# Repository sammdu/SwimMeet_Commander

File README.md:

# Swim Meet Commander

#### Unofficial macro keyboard for the [HY-TEK Swim Meet Manager](https://hytek.active.com/swim-meet-software.html) software.   

Designed with [KiCad](https://www.kicad-pcb.org/)   
Programmed with [Arduino](https://www.arduino.cc/)   

&nbsp;&nbsp;

## What Is This

A macro keyboard that controls the swim meet scoring software commonly used in American high-school and college swim meets. It simplifies operation of the software by pulling out 13 most used functionalities as dedicated keys, achieving one-key operation.

The device works by triggering keyboard shortcuts compatible with the swim meet software when a corresponding button is pushed. It is automatically recognized by most operating systems as an HID keyboard with no additional drivers required.

> 🔗 [See Technical Documentation on GitHub Wiki](https://github.com/sammdu/SwimMeet_Commander/wiki/Technical-Documentation)

## Assembled Device In-Operation

## 3D Renders

## TODO

* adjust button spacing to account for keycaps

## Materials

* Microcontroller: Digispark Development Board - [Amazon Vendor](https://www.amazon.com/DAOKI-Digispark-Kickstarter-ATTINY85-Development/dp/B01MDUHSWO) | [Official Page (Out of Stock)](http://digistump.com/products/1)
* Printed Circuit Board (PCB) | [Get Gerber Production Files](https://github.com/sammdu/SwimMeet_Commander/tree/master/KiCad/Gerbers)
* I/O Expander (to support 13 switches simultaneously): [Microchip MCP23017](https://www.digikey.com/product-detail/en/MCP23017T-E%2fSO/MCP23017T-E%2fSOCT-ND/5358289/)
* Keyboard Switches: [E-Switch KS1100](https://www.digikey.com/product-detail/en/KS1100OA1AF060/EG5505-ND/7364301/)
* Key Caps: [Sparkfun PRT-15305](https://www.sparkfun.com/products/15305), or any Cherry MX compatible models   
* USB Male-Female Cable: [Qualtek 3021056-01M](https://www.digikey.com/product-detail/en/3021056-01M/Q1104-ND/7795306/), or any compatible USB Type-A cable   
* Toggle Switch: [Sparkfun COM-09276](https://www.sparkfun.com/products/9276)
* SMD Slide Switch: [Sparkfun COM-10860](https://www.sparkfun.com/products/10860), or any compatible models
* 5mm LEDs
* 0805 SMD Resistors: `330R`, `4k7` and `10k` values
* Pin Headers

## Copyright & Licensing

This project consists of open source software and hardware, released under [Creative Commons Attribution 4.0 International License](http://creativecommons.org/licenses/by/4.0/), unless otherwise specified.   

This project is NOT endorsed or sponsored by HY-TEK Sports Software®, Active Network, LLC., or any of their affiliates.

**NOTE:**
```
THE SCHEMATICS, DESIGN, SOURCE FILES, SOFTWARE, AND DATASHEETS ARE PROVIDED "AS IS",
WITHOUT WARRANTY OF ANY KIND, EXPRESS OR IMPLIED, INCLUDING BUT NOT LIMITED TO
THE WARRANTIES OF MERCHANTABILITY, FITNESS FOR A PARTICULAR PURPOSE AND
NONINFRINGEMENT. IN NO EVENT SHALL THE AUTHORS OR COPYRIGHT HOLDERS BE LIABLE FOR
ANY CLAIM, DAMAGES OR OTHER LIABILITY, WHETHER IN AN ACTION OF CONTRACT, TORT
OR OTHERWISE, ARISING FROM, OUT OF OR IN CONNECTION WITH THE SCHEMATICS, DESIGN,
SOURCE FILES, SOFTWARE, AND DATASHEETS OR THE USE OR OTHER DEALINGS IN THE
SCHEMATICS, DESIGN, SOURCE FILES, SOFTWARE, AND DATASHEETS.
 ```

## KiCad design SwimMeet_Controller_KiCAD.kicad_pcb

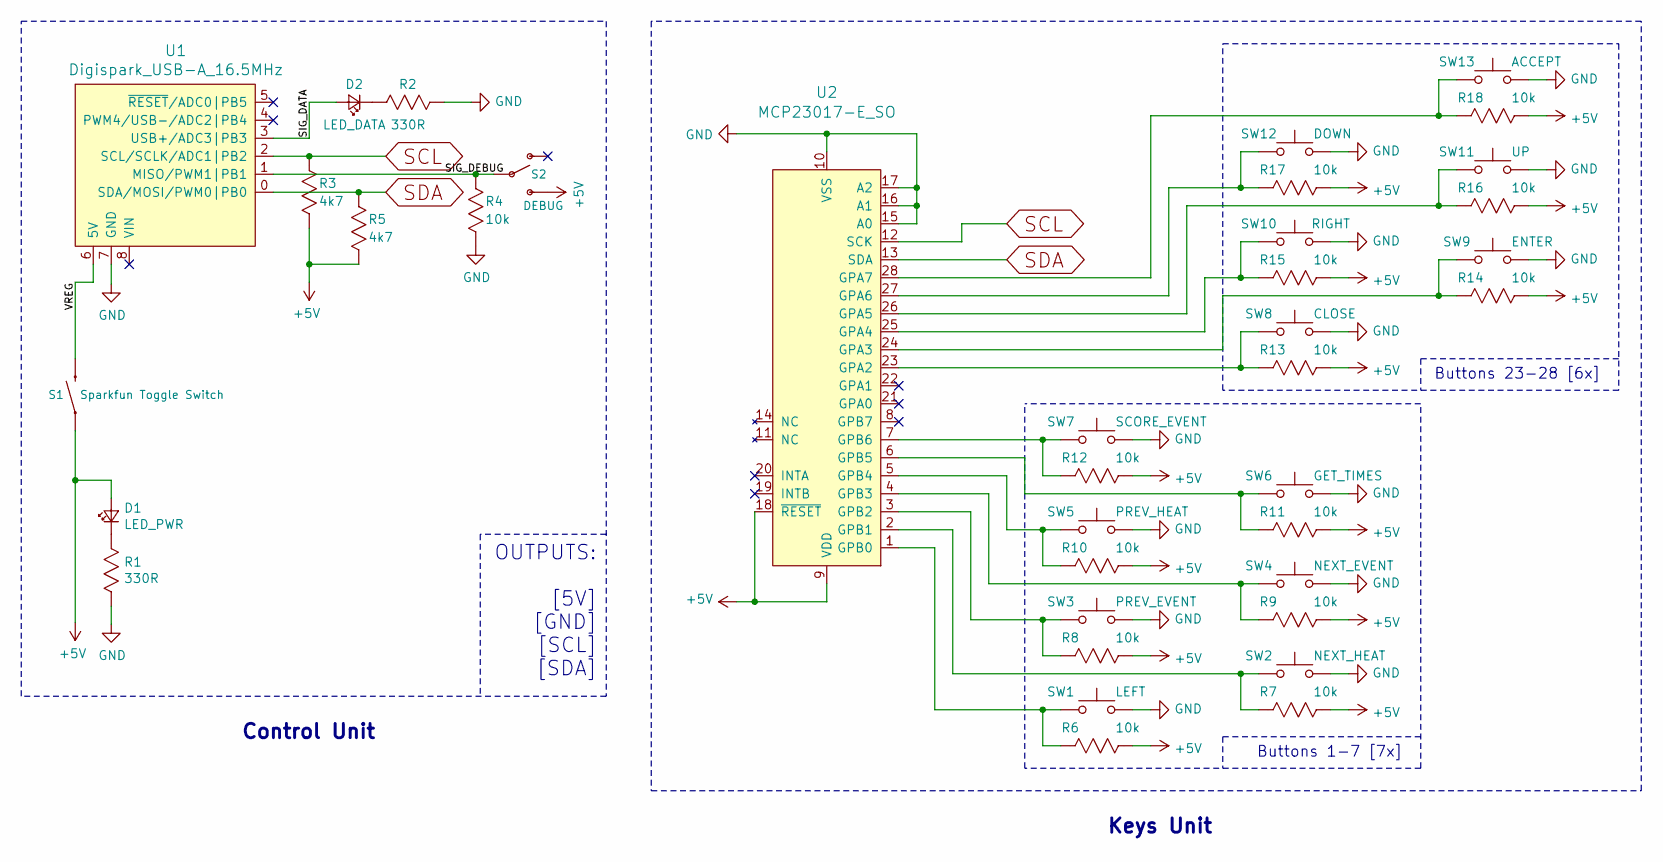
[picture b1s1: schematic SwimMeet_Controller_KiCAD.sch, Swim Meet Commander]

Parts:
D1: LED_PWR; LED_D5.0mm
D2: LED_DATA; LED_D5.0mm
R1, R2: 330R; R_0805_2012Metric_Pad1.15x1.40mm_HandSolder
R3, R5: 4k7; R_0805_2012Metric_Pad1.15x1.40mm_HandSolder
R4, R6, R7, R8, R9, R10, R11, R12, R13, R14, R15, R16, R17, R18: 10k; R_0805_2012Metric_Pad1.15x1.40mm_HandSolder
S1: Sparkfun Toggle Switch; TOGGLE_PANEL_COM-09276
S2: DEBUG; SWITCH_SPST_SMD_A
SW1: LEFT; SW_KeySwitch_KS1100_E-SWITCH
SW2: NEXT_HEAT; SW_KeySwitch_KS1100_E-SWITCH
SW3: PREV_EVENT; SW_KeySwitch_KS1100_E-SWITCH
SW4: NEXT_EVENT; SW_KeySwitch_KS1100_E-SWITCH
SW5: PREV_HEAT; SW_KeySwitch_KS1100_E-SWITCH
SW6: GET_TIMES; SW_KeySwitch_KS1100_E-SWITCH
SW7: SCORE_EVENT; SW_KeySwitch_KS1100_E-SWITCH
SW8: CLOSE; SW_KeySwitch_KS1100_E-SWITCH
SW9: ENTER; SW_KeySwitch_KS1100_E-SWITCH
SW10: RIGHT; SW_KeySwitch_KS1100_E-SWITCH
SW11: UP; SW_KeySwitch_KS1100_E-SWITCH
SW12: DOWN; SW_KeySwitch_KS1100_E-SWITCH
SW13: ACCEPT; SW_KeySwitch_KS1100_E-SWITCH
U1: Digispark_USB-A_16.5MHz; Digispark_USB-A
U2: MCP23017-E_SO; SOIC-28_W7.5mm; MPN MCP23017-E/SO; Digi-Key_PN MCP23017-E/SO-ND

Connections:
+5V: D1.2 (A), R3.2, R5.2, R6.1, R7.1, R8.1, R9.1, R10.1, R11.1, R12.1, R13.1, R14.1, R15.1, R16.1, R17.1, R18.1, S1.1, S2.3 (S), U2.9 (VDD), U2.18 (~RESET)
/SIG_DATA: D2.2 (A), U1.3 (USB+/ADC3|PB3)
/SIG_DEBUG: R4.1, S2.2, U1.1 (MISO/PWM1|PB1)
/VREG: S1.2, U1.6 (5V)
GND: R1.2, R2.2, R4.2, S2.GND1, S2.GND2, S2.GND3, S2.GND4, SW1.2, SW2.2, SW3.2, SW4.2, SW5.2, SW6.2, SW7.2, SW8.2, SW9.2, SW10.2, SW11.2, SW12.2, SW13.2, U1.7 (GND), U2.10 (VSS), U2.15 (A0), U2.16 (A1), U2.17 (A2)
unnamed: D1.1 (K), R1.1
unnamed: D2.1 (K), R2.1
unnamed: R6.2, SW1.1, U2.1 (GPB0)
unnamed: R7.2, SW2.1, U2.2 (GPB1)
unnamed: R8.2, SW3.1, U2.3 (GPB2)
unnamed: R9.2, SW4.1, U2.4 (GPB3)
unnamed: R10.2, SW5.1, U2.5 (GPB4)
unnamed: R11.2, SW6.1, U2.6 (GPB5)
unnamed: R12.2, SW7.1, U2.7 (GPB6)
unnamed: R13.2, SW8.1, U2.23 (GPA2)
unnamed: R14.2, SW9.1, U2.24 (GPA3)
unnamed: R15.2, SW10.1, U2.25 (GPA4)
unnamed: R16.2, SW11.1, U2.26 (GPA5)
unnamed: R17.2, SW12.1, U2.27 (GPA6)
unnamed: R18.2, SW13.1, U2.28 (GPA7)
SCL: R3.1, U1.2 (SCL/SCLK/ADC1|PB2), U2.12 (SCK)
SDA: R5.1, U1.0 (SDA/MOSI/PWM0|PB0), U2.13 (SDA)

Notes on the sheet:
OUTPUTS: [5V] [GND] [SCL] [SDA]
Buttons 1-7 [7x]
Buttons 23-28 [6x]
Control Unit
Keys Unit

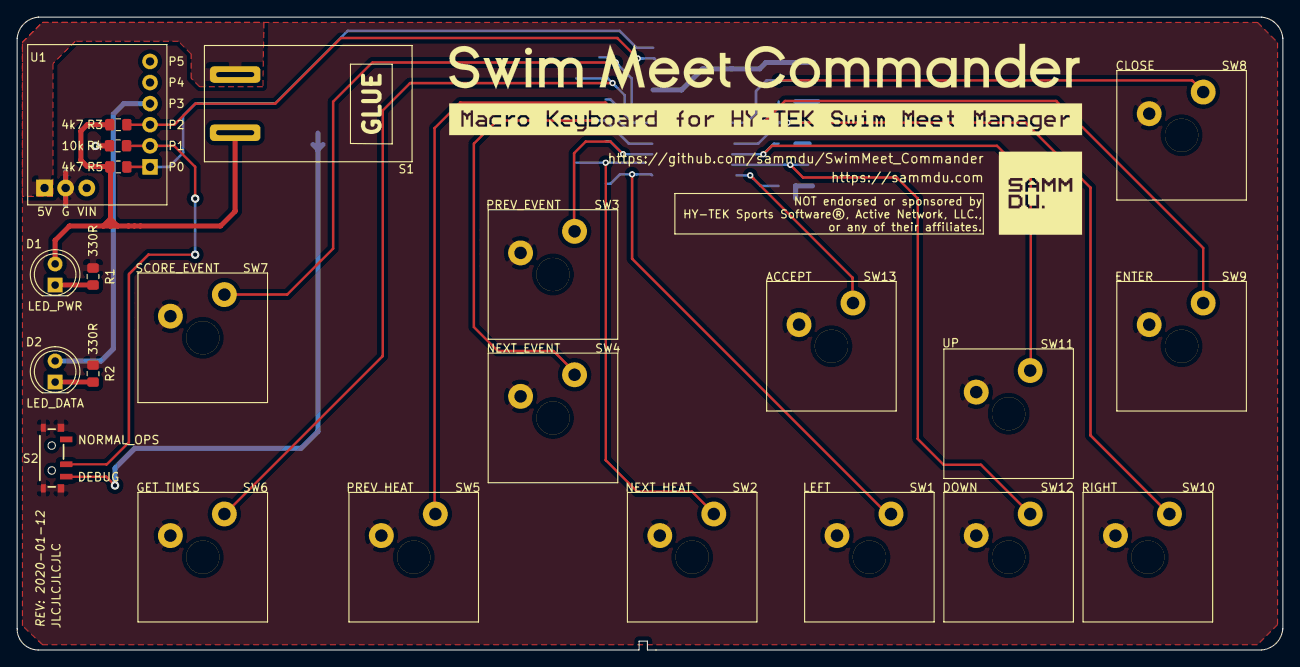
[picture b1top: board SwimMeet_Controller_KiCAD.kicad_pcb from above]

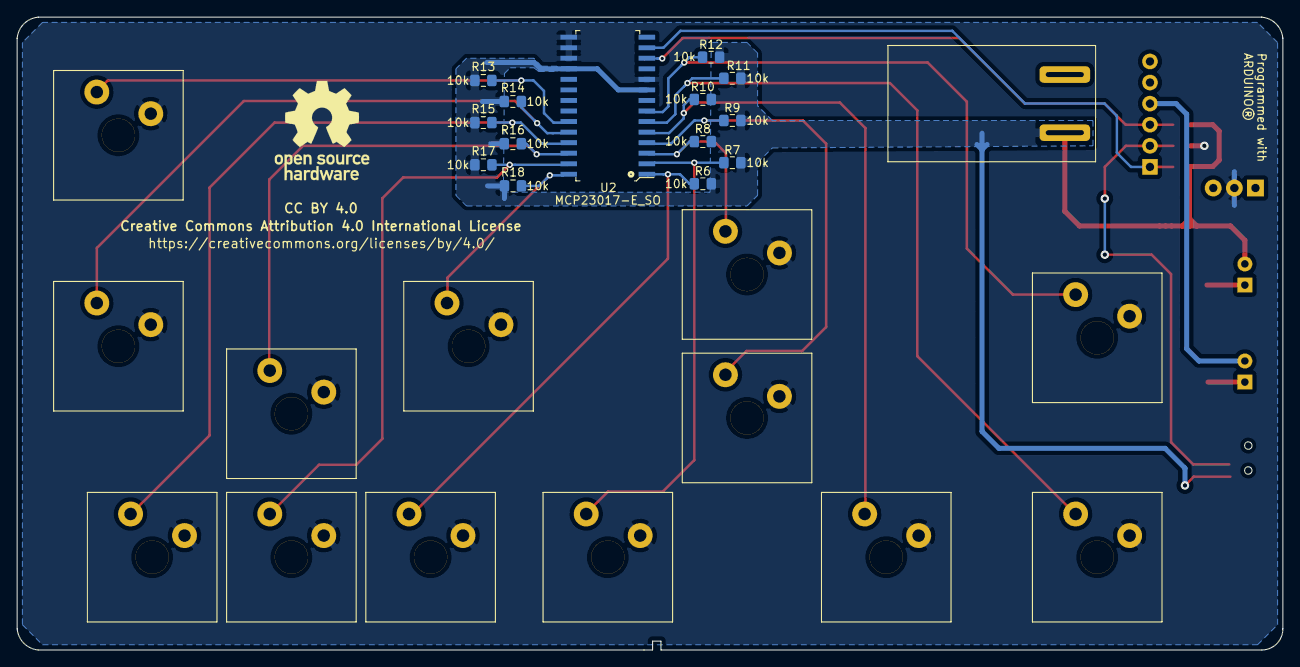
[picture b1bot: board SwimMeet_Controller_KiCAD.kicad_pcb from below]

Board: 2 copper layers, 152.4 x 76.2 mm, 37 parts (14 on the bottom side), 22 nets.

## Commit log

2019-12-27 initial commit 2019-12-27
2019-12-27 added 3d images for the README
2019-12-27 include 3D renders in README
2019-12-27 added materials to README
2019-12-27 added CC license badge
2019-12-27 update CC icon
2019-12-27 add KiCad credit to README
2019-12-27 update copyright info
2019-12-27 added OSHW, moved CC, augmented COPYRIGHT NOTE; README
2019-12-27 augmented spacing for OSHW & CC logos; README
2019-12-28 used proper power symbols in schem; made schem compatible with larger grid size; added net names; tidy'ed up PCB more
2019-12-28 added toggle switch to materials in README
2019-12-28 updated PCB renders
2019-12-30 implemented polygons for 5V+ net
2020-01-01 improved power LED connection; updated front silk screen; updated titleblock
2020-01-03 added TODO item: debug switch
2020-01-07 updated TODO list
2020-01-08 updated TODO
2020-01-08 adjusted resistor values, updated F.Silk graphic, updated toggle switch footprint
2020-01-08 check off TODO list items
2020-01-09 updated resistor values in README
2020-01-13 MAJOR REVISION 2020-01-12
2020-01-13 restructured directory
2020-01-13 appended new README
2020-01-13 re-appended Gerbers and PDFs
2020-01-13 added TODO item
2020-01-13 adjusted debouncing; adjusted polling logic;
2020-01-13 clear TODO list
2020-01-20 updated 3D model for Digispark; updated 3D render in README
2020-01-20 updated materials description
2020-01-20 updated Digispark 3D model and README image
2020-01-23 updated Open Source Hardware logo
2020-02-04 renamed the Pictures folder; included assembled in-operation picture
2020-02-07 amended schematic and added pictures for the wiki
2020-02-07 added picture of the debug switch location
2020-02-08 update schematic PDF and image
2020-02-08 include debug output sample screenshot
2020-02-08 added link incon to documentation link

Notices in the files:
README.md:
CC BY 4.0
SwimMeet_Controller_KiCAD.kicad_pcb:
https://creativecommons.org/licenses/by/4.0
